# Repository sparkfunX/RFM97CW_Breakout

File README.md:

SparkFun RFM97C Mini Shield LoRa - 100mW
========================================

[*SparkFun RFM97C Mini Shield LoRa - 100mW (SPX-18574)*](https://www.sparkfun.com/products/18574)

The RFM97C is a great little module that incorporates the [SX1276 LoRa transceiver](https://www.semtech.com/products/wireless-rf/lora-core/sx1276) from Semtech. LoRa is best for long range communication (hundreds of feet), low power, and low data rates (~500bps). This 'Mini Shield' is designed to be attached to the top or bottom of any of our Thing Plus boards. Pictured is the [ESP32 Thing Plus](https://www.sparkfun.com/products/18018). We include a PTH soldering point for a low cost wire antenna (~3" for 915MHz) along side a stress relief hole. For folks that need a bit more oomph, there is a U.FL connector available for larger, external RP-SMA LoRa antennas.

Our example sketches make quick work of the initial setup, and the RadioLib Arduino Library makes advanced configuration and [protocols](https://github.com/jgromes/RadioLib/wiki/Default-configuration#protocols) (AX.25, Hellschreiber, Morse, RTTY, and SSTV) a cinch too!

Repository Contents
-------------------

* **/Documents** - Datasheets and mechanical drawings
* **/Firmware** - Example sketch(es)
* **/Hardware** - All Eagle design files (.brd, .sch, .STL)

Product Versions
----------------

* [SPX-18574](https://www.sparkfun.com/products/18574)

License Information
-------------------

This product is _**open source**_! 

Please review the LICENSE.md file for license information. 

If you have any questions or concerns on licensing, please contact technical support on our [SparkFun forums](https://forum.sparkfun.com/viewforum.php?f=152).

Distributed as-is; no warranty is given.

- Your friends at SparkFun.

_<COLLABORATION CREDIT>_

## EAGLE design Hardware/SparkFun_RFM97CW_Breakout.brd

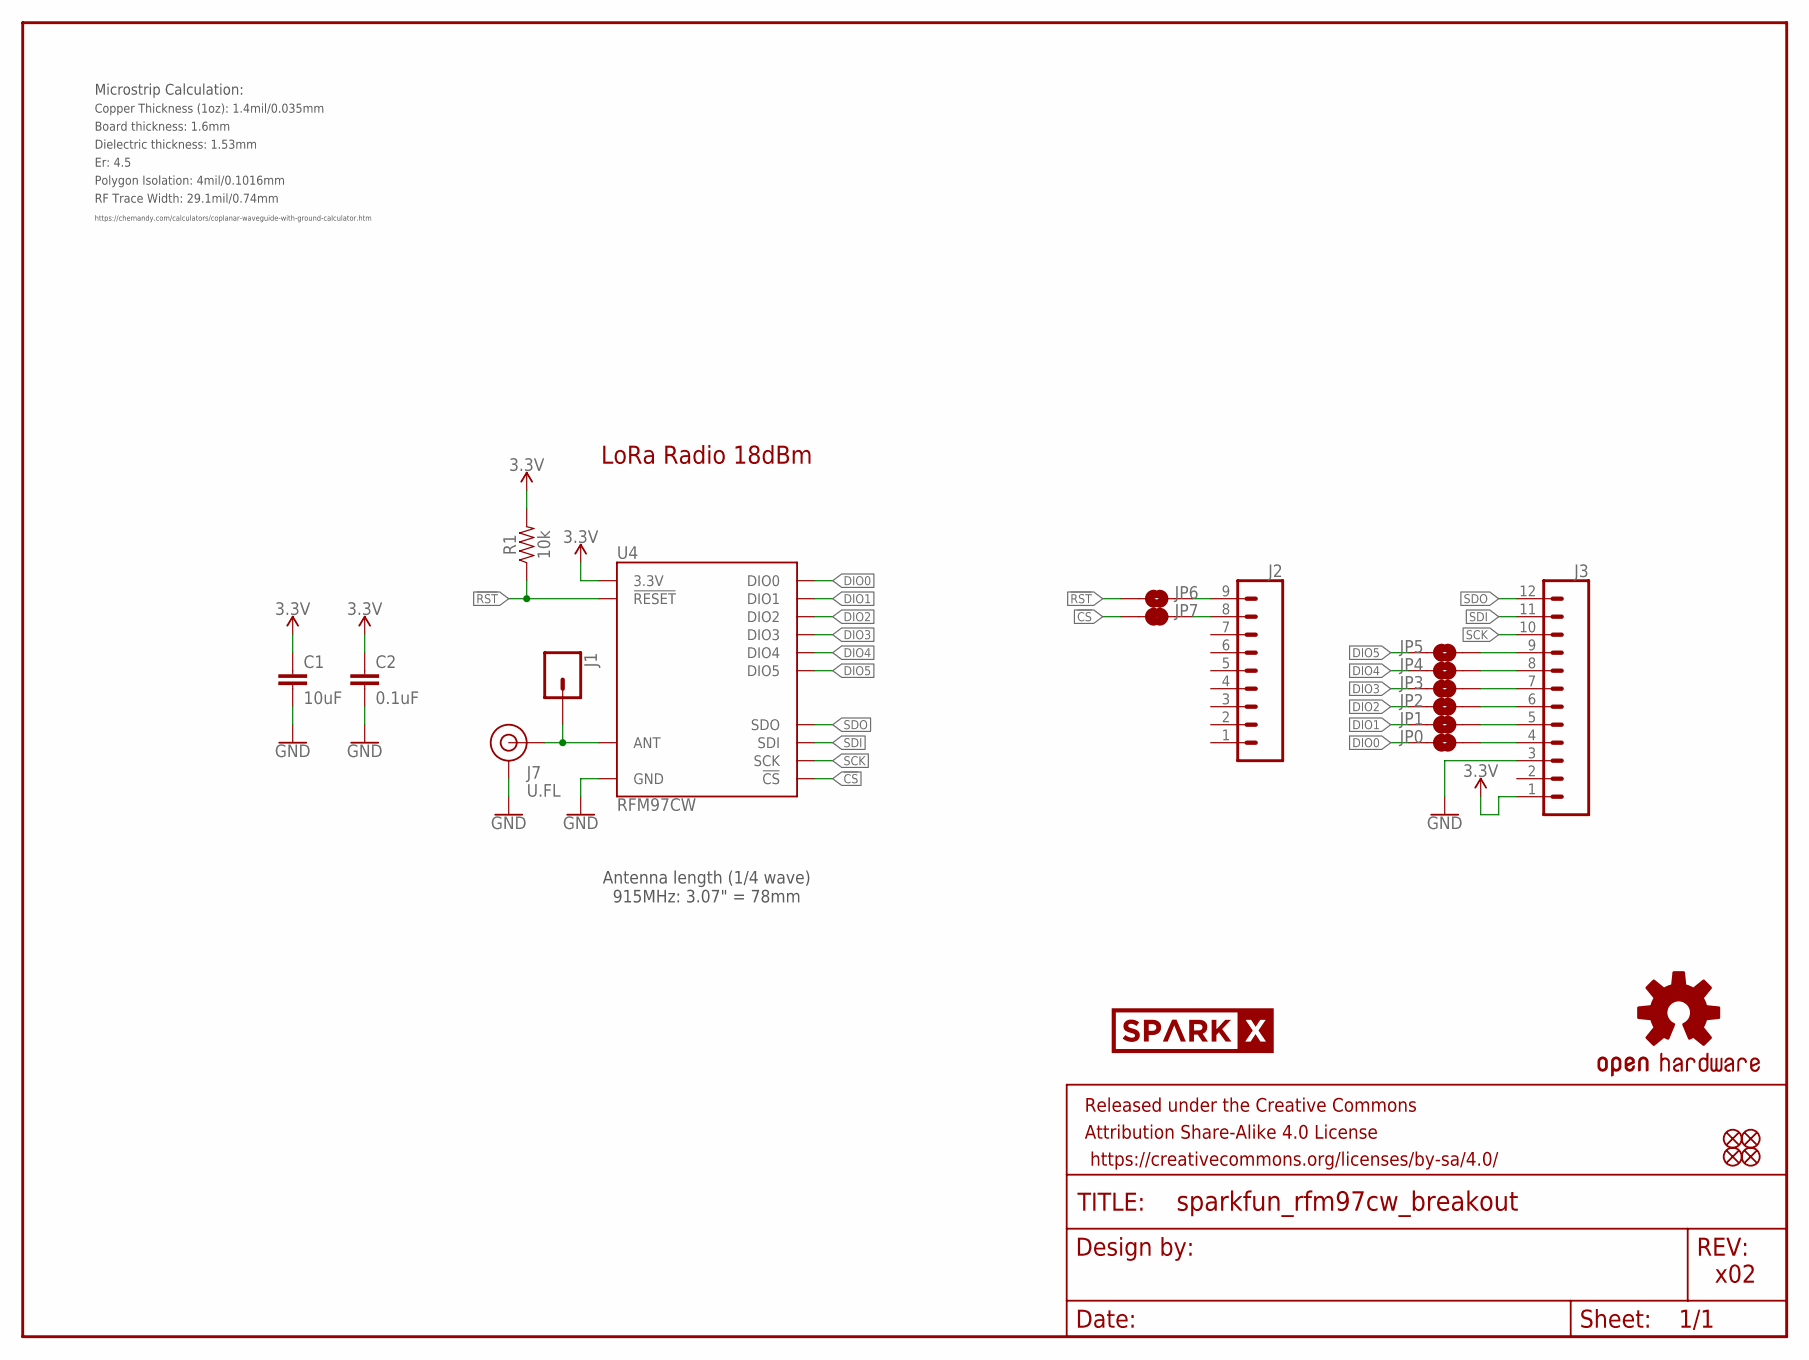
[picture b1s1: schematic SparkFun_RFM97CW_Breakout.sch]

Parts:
C1: 10uF; 0603
C2: 0.1uF; 0603
FID1, FID2, FID3, FID4: FIDUCIAL1X2; FIDUCIAL-1X2
FRAME1: FRAME-LETTER; CREATIVE_COMMONS
J1: CONN_01PTH_NO_SILK_YES_STOP; 1X01_NO_SILK
J2: CONN_09NO_SILK; 1X09_NO_SILK
J3: CONN_12NO_SILK; 1X12_NO_SILK
J7: U.FL
JP0, JP1, JP2, JP3, JP4, JP5, JP6: JUMPER-SMT_2_NO_NO-SILK; SMT-JUMPER_2_NO_NO-SILK
JP7: JUMPER-SMT_2_NC_TRACE_NO-SILK; SMT-JUMPER_2_NC_TRACE_NO-SILK
LOGO2: OSHW-LOGOS; OSHW-LOGO-S
R1: 10k; 0603
U4: RFM97CW; RFM97
U$22: SPARKX-LOGO5; SPARKX-LARGE

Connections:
3.3V: C1.1, C2.1, J3.1, R1.2, U4.3V3 (3.3V)
!CS!: JP7.1, U4.!CS!
!RST!: JP6.1, R1.1, U4.!RST (!RESET)
ANT: J1.1, J7.FEED (SIGNAL), U4.ANT
DIO0: JP0.1, U4.DIO0
DIO1: JP1.1, U4.DIO1
DIO2: JP2.1, U4.DIO2
DIO3: JP3.1, U4.DIO3
DIO4: JP4.1, U4.DIO4
DIO5: JP5.1, U4.DIO5
GND: C1.2, C2.2, J3.3, J7.1 (GND), J7.2 (GND), U4.GND, U4.GND@1 (GND), U4.GND@2 (GND)
unnamed: J3.6, JP2.2
unnamed: J2.9, JP6.2
unnamed: J2.8, JP7.2
unnamed: J3.5, JP1.2
unnamed: J3.4, JP0.2
unnamed: J3.7, JP3.2
unnamed: J3.8, JP4.2
unnamed: J3.9, JP5.2
SCK: J3.10, U4.SCK
SDI: J3.11, U4.SDI
SDO: J3.12, U4.SDO

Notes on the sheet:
x02
Antenna length (1/4 wave) 915MHz: 3.07" = 78mm
Board thickness: 1.6mm
Er: 4.5
Copper Thickness (1oz): 1.4mil/0.035mm
RF Trace Width: 29.1mil/0.74mm
Polygon Isolation: 4mil/0.1016mm
Dielectric thickness: 1.53mm
https://chemandy.com/calculators/coplanar-waveguide-with-ground-calculator.htm
Microstrip Calculation:
LoRa Radio 18dBm

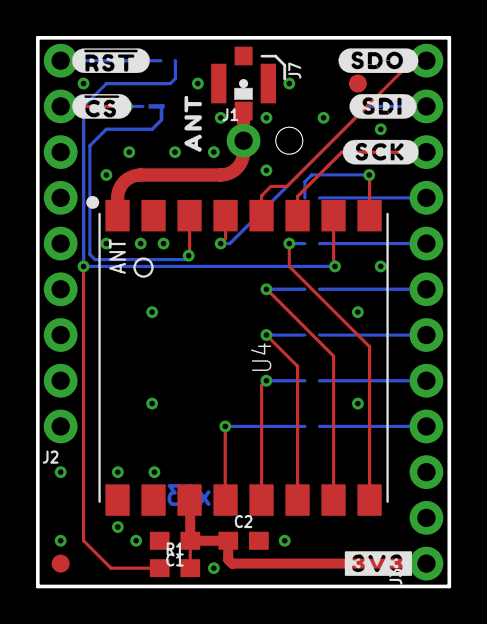
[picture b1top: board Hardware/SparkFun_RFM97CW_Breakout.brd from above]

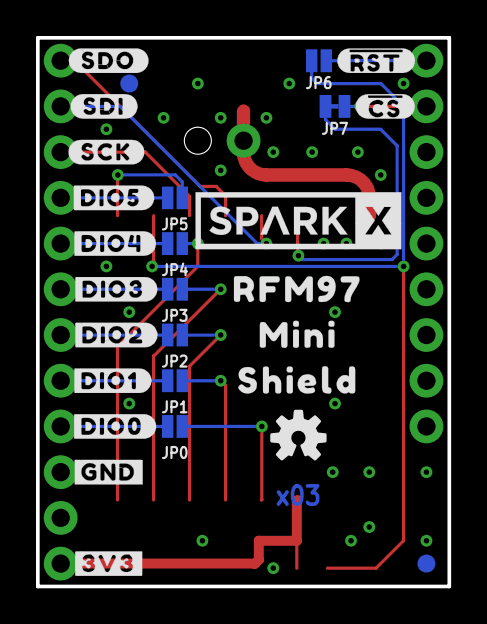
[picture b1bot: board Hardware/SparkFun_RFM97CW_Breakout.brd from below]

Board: 2 copper layers, 22.9 x 30.5 mm, 46 parts (28 on the bottom side), 22 nets.

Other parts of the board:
U$1: ANT0
U$2, U$21: ##CS##2
U$3, U$7: #SDO#0
U$4, U$6: #SDI#1
U$5, U$12: #SCK#0
U$8, U$9: #3V3#0
U$10: #GND#1
U$11: MINI0
U$13, U$17: ##RST##0
U$19: RFM970
U$20: SHIELD2
U$23: #DIO0#0
U$24: #DIO1#0
U$25: #DIO2#0
U$26: #DIO3#0
U$27: #DIO4#0
U$28: #DIO5#0

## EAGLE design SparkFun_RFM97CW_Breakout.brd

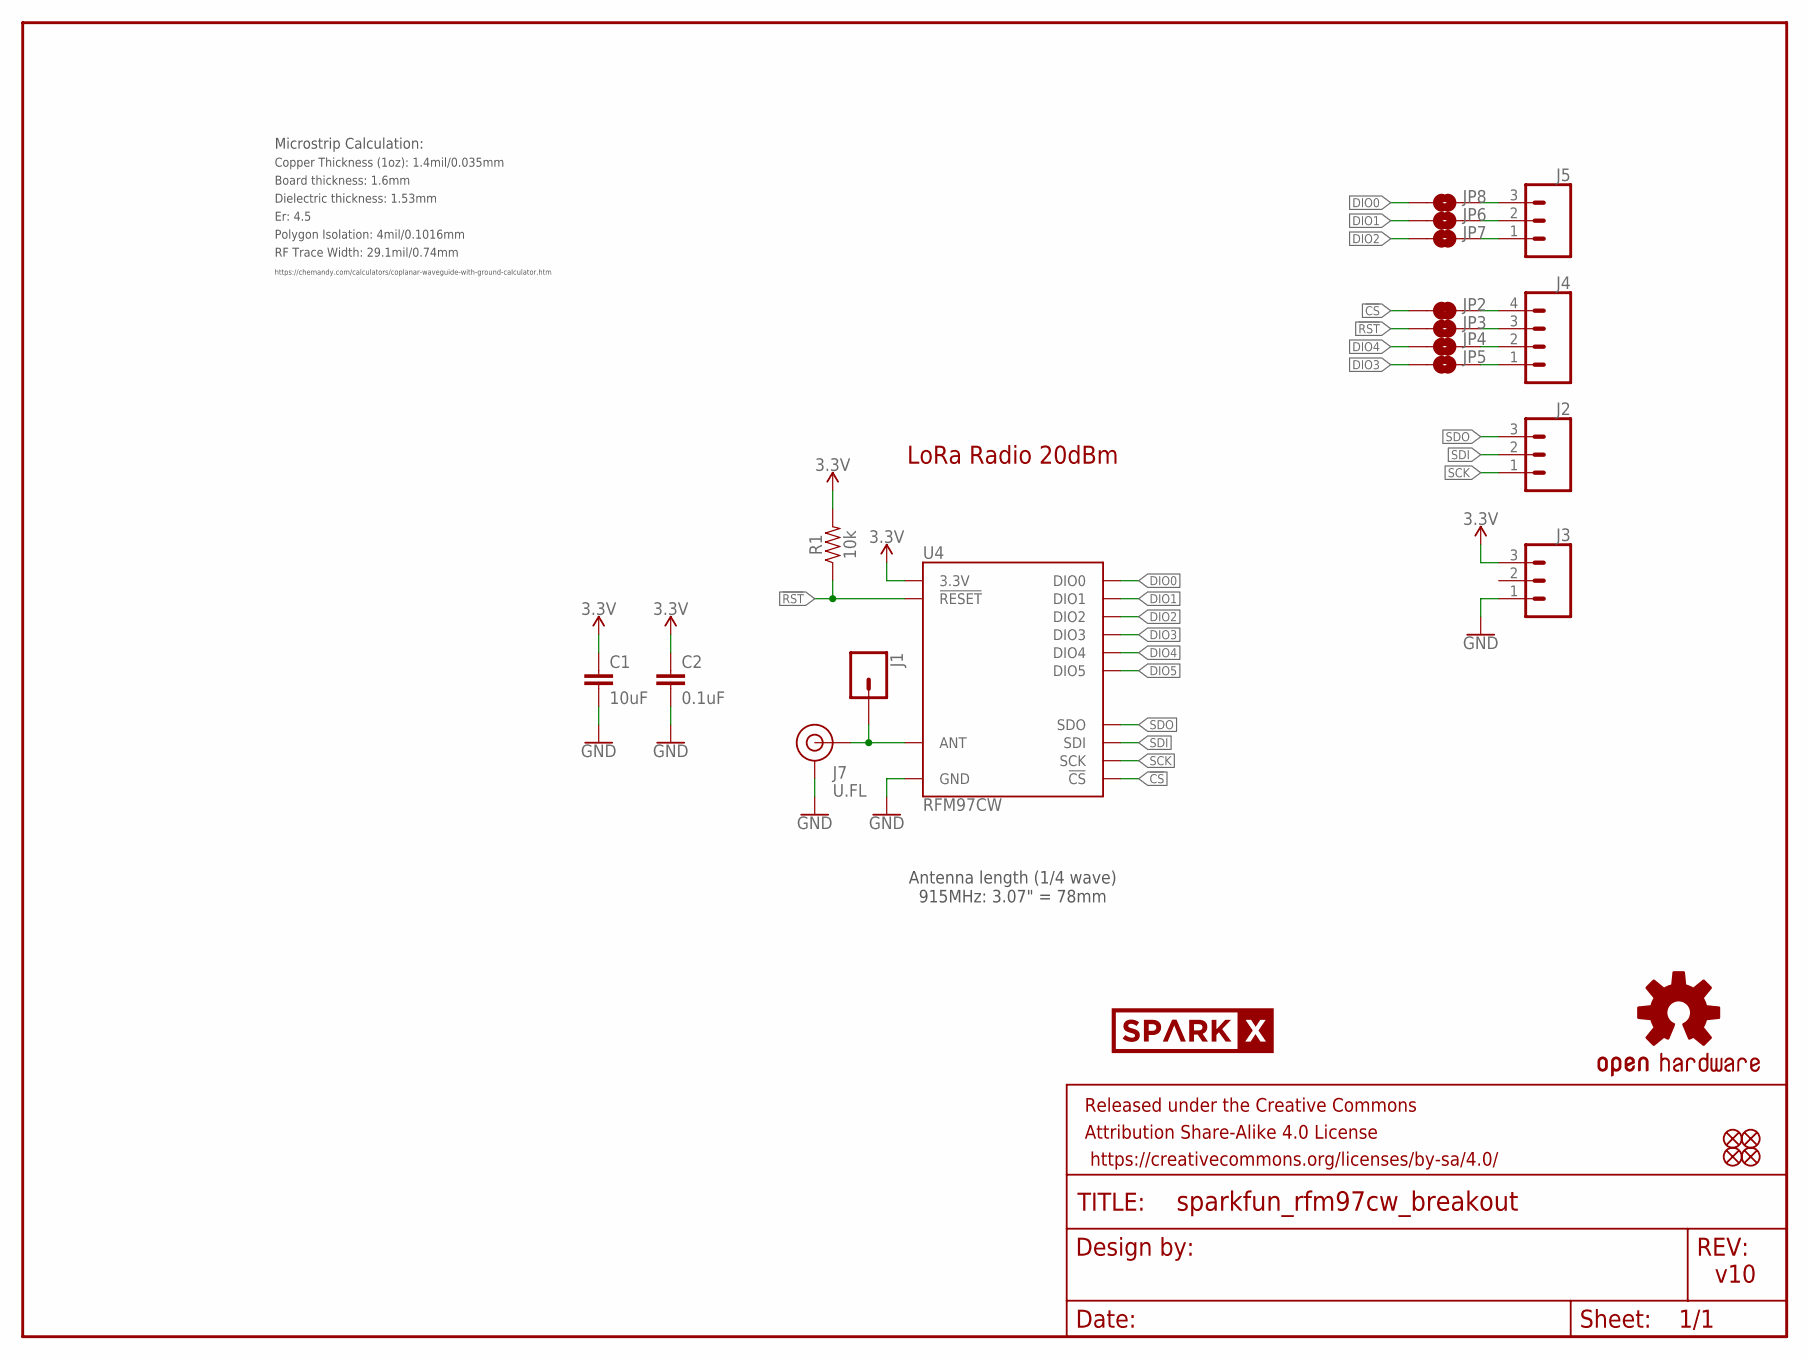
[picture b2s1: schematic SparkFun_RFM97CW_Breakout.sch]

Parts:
C1: 10uF; 0603
C2: 0.1uF; 0603
FID1, FID2, FID3, FID4: FIDUCIAL1X2; FIDUCIAL-1X2
FRAME1: FRAME-LETTER; CREATIVE_COMMONS
J1: CONN_01PTH_NO_SILK_YES_STOP; 1X01_NO_SILK
J2, J3, J5: CONN_031X03_NO_SILK; 1X03_NO_SILK
J4: CONN_041X04_NO_SILK; 1X04_NO_SILK
J7: U.FL
JP2: JUMPER-SMT_2_NC_TRACE_NO-SILK; SMT-JUMPER_2_NC_TRACE_NO-SILK
JP3, JP4, JP5, JP6, JP7, JP8: JUMPER-SMT_2_NO_NO-SILK; SMT-JUMPER_2_NO_NO-SILK
LOGO2: OSHW-LOGOS; OSHW-LOGO-S
R1: 10k; 0603
U4: RFM97CW; RFM97
U$22: SPARKX-LOGO5; SPARKX-LARGE

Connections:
3.3V: C1.1, C2.1, J3.3, R1.2, U4.3V3 (3.3V)
!CS!: JP2.1, U4.!CS!
!RST!: JP3.1, R1.1, U4.!RST (!RESET)
ANT: J1.1, J7.FEED (SIGNAL), U4.ANT
DIO0: JP8.1, U4.DIO0
DIO1: JP6.1, U4.DIO1
DIO2: JP7.1, U4.DIO2
DIO3: JP5.1, U4.DIO3
DIO4: JP4.1, U4.DIO4
DIO5: U4.DIO5
GND: C1.2, C2.2, J3.1, J7.1 (GND), J7.2 (GND), U4.GND, U4.GND@1 (GND), U4.GND@2 (GND)
unnamed: J5.3, JP8.2
unnamed: J4.4, JP2.2
unnamed: J4.3, JP3.2
unnamed: J4.2, JP4.2
unnamed: J4.1, JP5.2
unnamed: J5.2, JP6.2
unnamed: J5.1, JP7.2
SCK: J2.1, U4.SCK
SDI: J2.2, U4.SDI
SDO: J2.3, U4.SDO

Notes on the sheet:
v10
Antenna length (1/4 wave) 915MHz: 3.07" = 78mm
Board thickness: 1.6mm
Er: 4.5
Copper Thickness (1oz): 1.4mil/0.035mm
RF Trace Width: 29.1mil/0.74mm
Polygon Isolation: 4mil/0.1016mm
Dielectric thickness: 1.53mm
https://chemandy.com/calculators/coplanar-waveguide-with-ground-calculator.htm
Microstrip Calculation:
LoRa Radio 20dBm

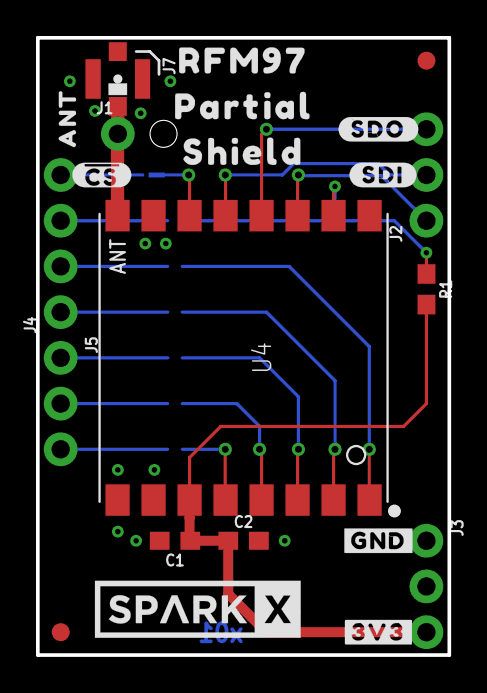
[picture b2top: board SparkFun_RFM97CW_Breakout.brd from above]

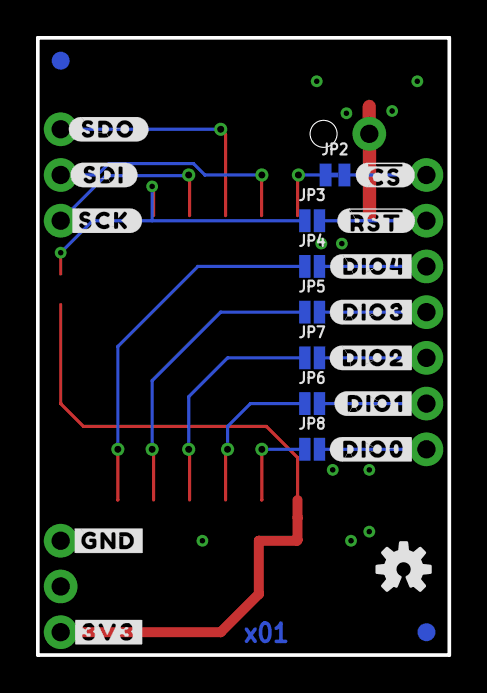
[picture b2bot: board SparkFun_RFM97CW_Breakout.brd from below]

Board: 2 copper layers, 22.9 x 34.3 mm, 45 parts (22 on the bottom side), 20 nets.

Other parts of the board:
U$1: ANT0
U$2, U$21: ##CS##2
U$3, U$7: #SDO#0
U$4, U$6: #SDI#1
U$5: #SCK#2
U$8, U$9: #3V3#0
U$10, U$11: #GND#1
U$12: #DIO0#5
U$13: #DIO1#4
U$14: #DIO2#3
U$15: #DIO3#2
U$16: #DIO4#1
U$17: ##RST##0
U$18: PARTIAL1
U$19: RFM970
U$20: SHIELD2

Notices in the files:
parts and their libraries:
SparkFun-Aesthetics: Licensing: CC v3.0 Share-Alike You are welcome to use this library for commercial purposes.
SparkFun-RF: Licensing: Creative Commons ShareAlike 4.0 International - https://creativecommons.org/licenses/by-sa/4.0
SparkFun-Aesthetics: https://creativecommons.org/licenses/by-sa/4.0
